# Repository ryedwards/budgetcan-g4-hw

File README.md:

# BudgetCAN G4

Hardware files for a simple CAN and LIN device built around an STM32 G4 MCU

## Description

The BudgetCAN G4 Hardware is designed to implement the full CAN potential of the STM32G4 MCU.  The hardware has been designed with the following features:
* USB-C connector for robust connectivity to a host machine
* 3 CANFD channels each with SW selectable termination resistors
* 1 LIN channel with SW selectable master pull-up
* 12V power input provides power for LIN and a 3A 5V regulator
* Debug header pinout for STLINK v3 Mini 14-pin connector - the VCP pins are routed to a UART for debugging
* Onboard 8Mhz crystal provides high clock accuracy for CANFD
* 5V power MUX to ensure graceful handoff between USB and 12V power supplies
* 3x configurable LEDs for status indications
* Automotive grade Molex Mini50 connector
* 4 layer PCB
* BOM cost under $15USD

## File usage

* The HW was designed with KiCad8
* Part BOM included with the schematic is complete for JLCPCB parts

## Firmware
Firmware is available for this hardware in the budgetcan firmware repository.  This firmware is based on the gs_usb driver and currently is fully supported in Linux and will work in Windows using the same drivers that have been developed for gs_usb.
* https://github.com/ryedwards/budgetcan-fw

You can also use the included STM32CubeMX .ioc file to generate your own firmware.  

This hardware can also be used as a standalone device (gateway module, simulated ECU, etc) since it has a 12V input and can be used headless.

## Help

If you find any issues with the hardware please submit an issue into GitHub

## License

This project is licensed under the MIT License - see the LICENSE.md file for details

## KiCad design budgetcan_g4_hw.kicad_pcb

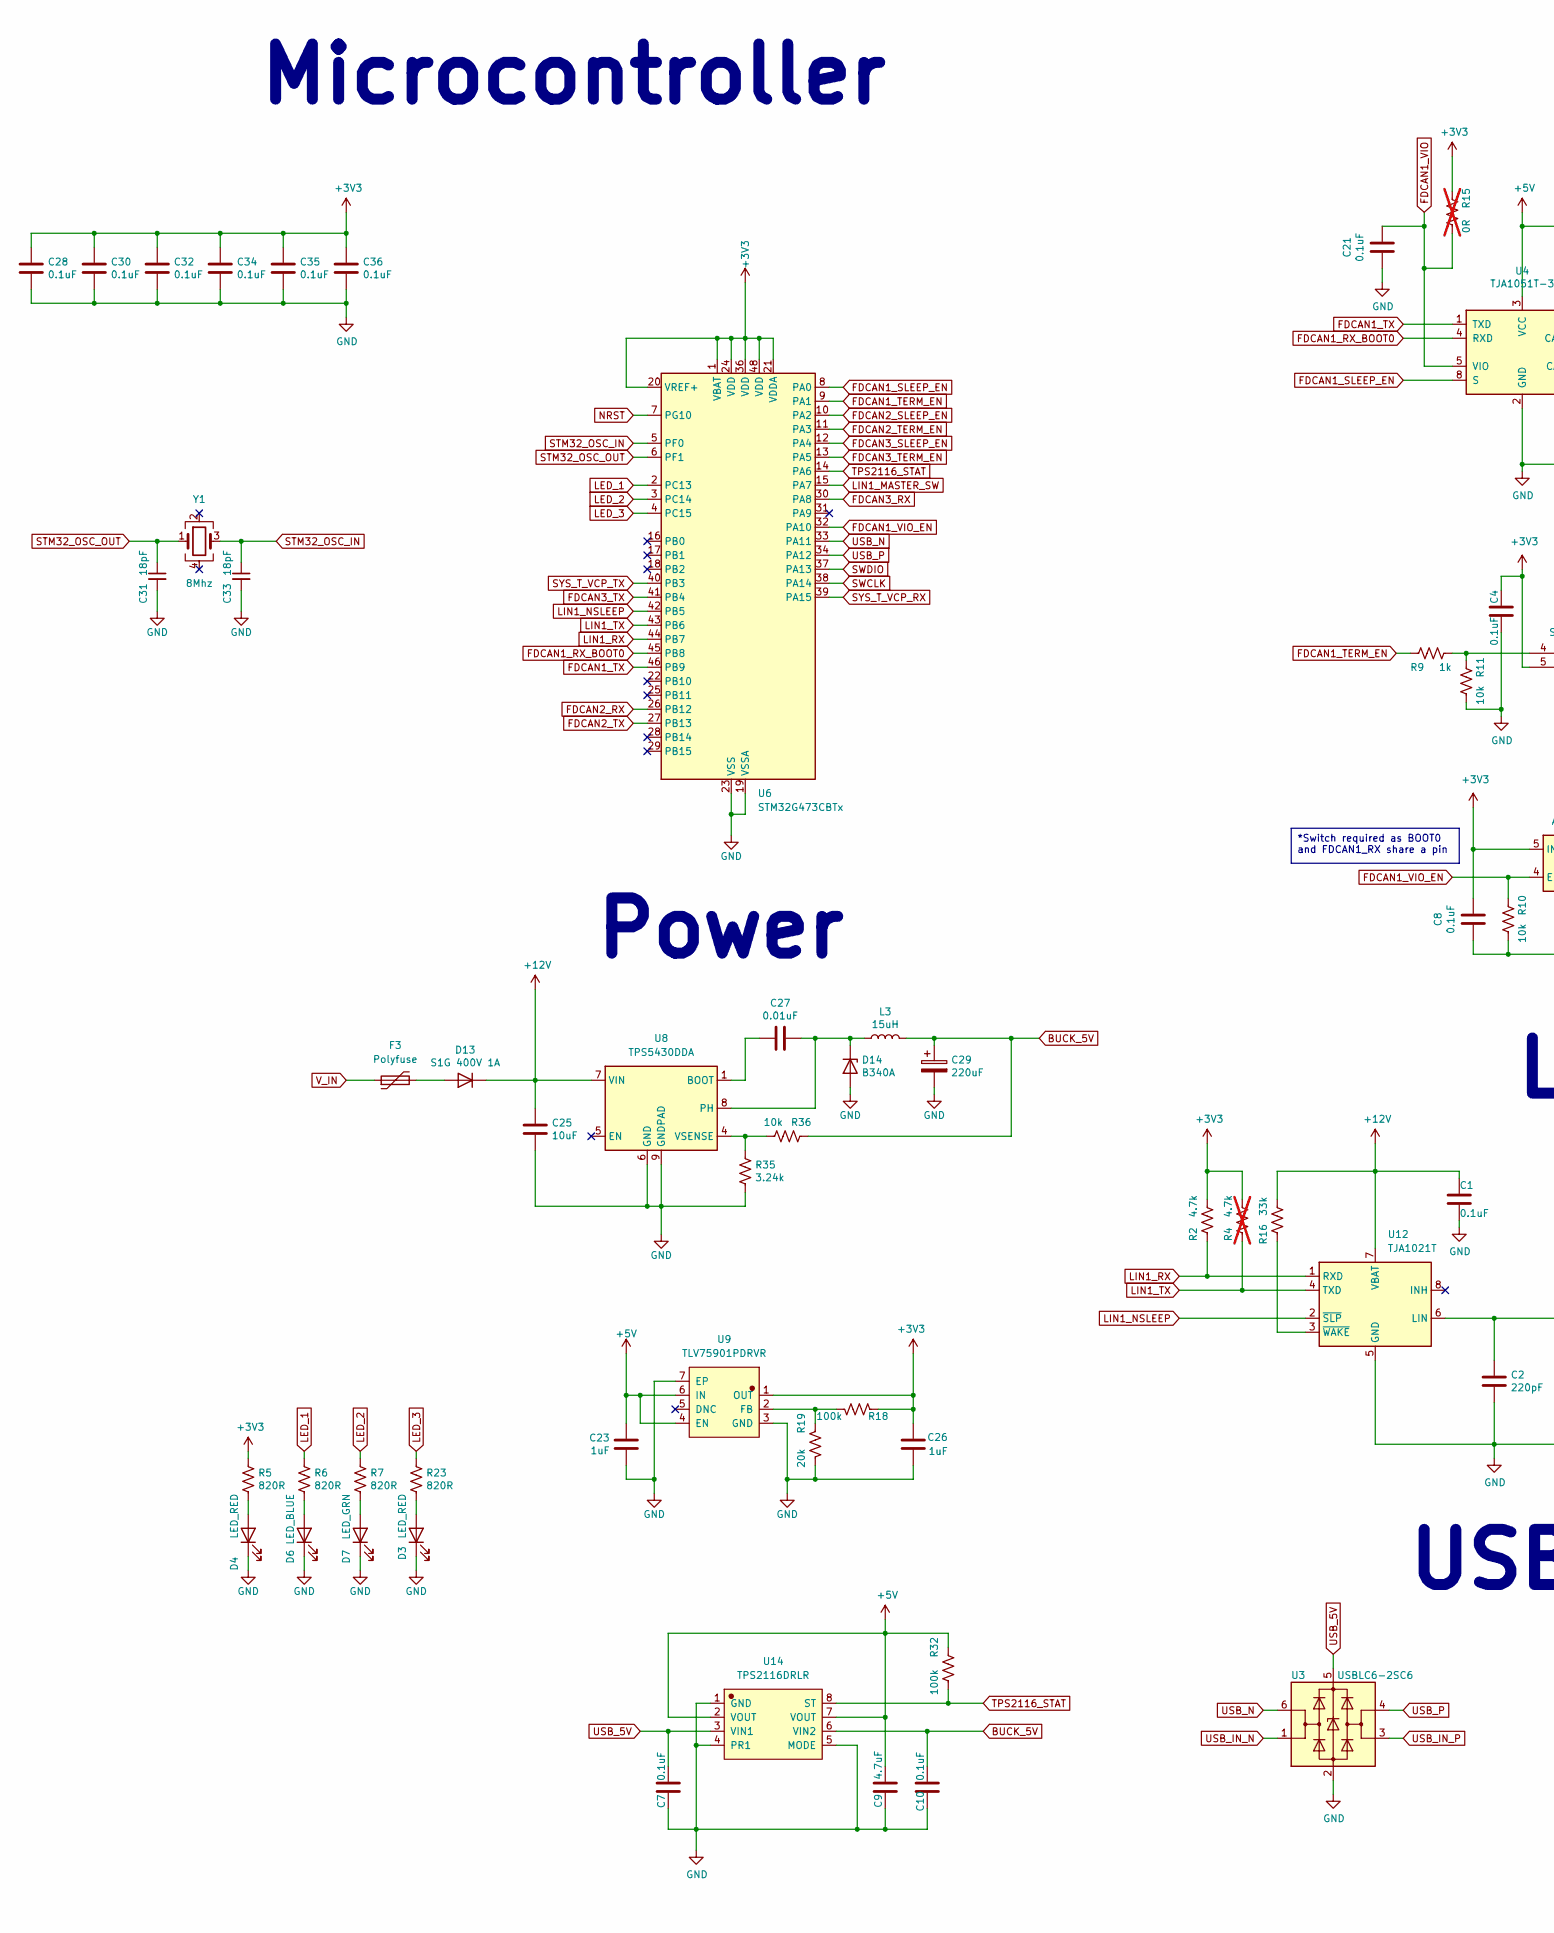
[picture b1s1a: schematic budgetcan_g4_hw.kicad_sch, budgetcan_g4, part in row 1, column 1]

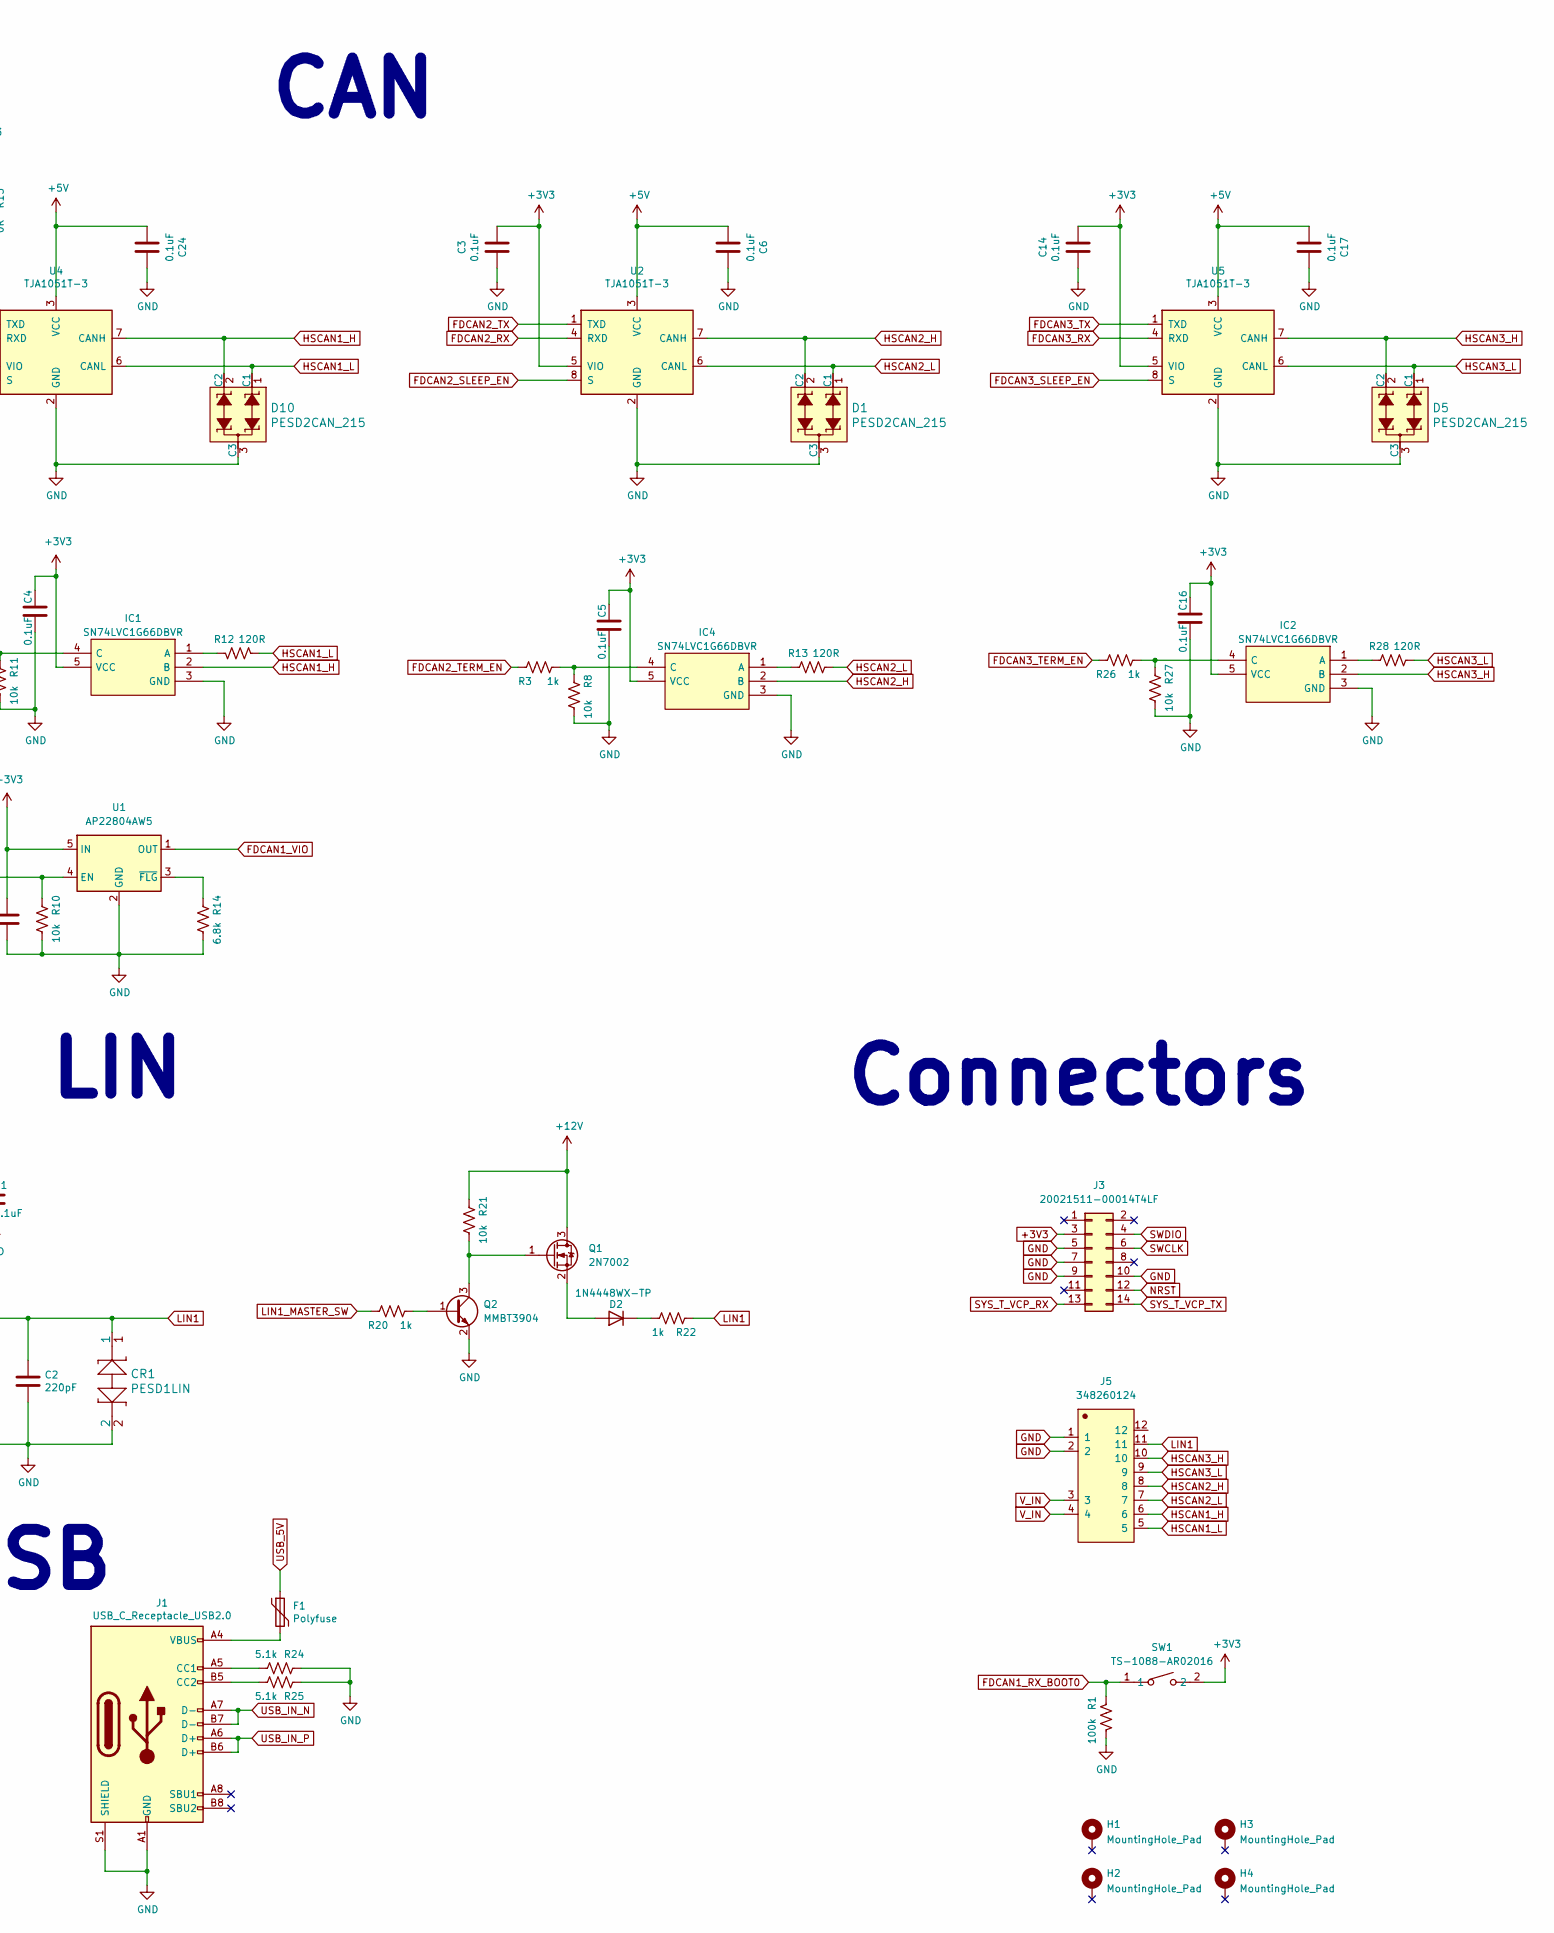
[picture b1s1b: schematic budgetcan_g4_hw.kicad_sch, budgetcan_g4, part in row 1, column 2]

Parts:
C1, C3, C4, C5, C6, C8, C14, C16, C17, C21, C24: 0.1uF; C_0402_1005Metric; Manufacturer_Part_Number CC0603KRX7R8BB104; LCSC Part # C1525
C2: 220pF; C_0402_1005Metric; Manufacturer_Part_Number CC0603JRNPO9BN221; LCSC Part # C1530
C7, C10: 0.1uF; C_0603_1608Metric; Manufacturer_Part_Number CC0603KRX7R8BB104; LCSC Part # C14663
C9: 4.7uF; C_0603_1608Metric; LCSC Part # C19666
C23, C26: 1uF; C_0603_1608Metric; LCSC Part # C15849
C25: 10uF; C_1206_3216Metric; Manufacturer_Part_Number CL31B106KQHNFNE; LCSC Part # C13585
C27: 0.01uF; C_0603_1608Metric; LCSC Part # C57112
C28, C30, C32, C34, C35, C36: 0.1uF; C_0402_1005Metric; LCSC Part # C1525
C29: 220uF; CP_Elec_6.3x5.4; LCSC Part # C88676
C31, C33: 18pF; C_0402_1005Metric; LCSC Part # C1549
CR1: PESD1LIN; D_SOD-323; Manufacturer_Part_Number PESD1LIN,135; LCSC Part # C2831530
D1, D5, D10: PESD2CAN_215; SOT-23; MPN PESD2CAN,215; Digi-Key_PN 1727-3891-1-ND
D2: ‎1N4448WX-TP‎; D_SOD-323; Manufacturer_Part_Number ‎1N4448WX-TP‎; Digi-Key_PN 1N4448WXTPMSCT-ND
D3, D4: LED_RED; LED_0805_2012Metric; LCSC Part # C84256
D6: LED_BLUE; LED_0805_2012Metric; LCSC Part # C965817
D7: LED_GRN; LED_0805_2012Metric; LCSC Part # C2297
D13: S1G 400V 1A; D_SMA; Manufacturer_Part_Number S1G; LCSC Part # C95872
D14: B340A; D_SMA; LCSC Part # C3018525
F1: Polyfuse; Fuse_0805_2012Metric; Manufacturer_Part_Number 0ZCK0035FF2G; LCSC Part # C2833485
F3: Polyfuse; F1812; Manufacturer_Part_Number 0ZCG0200AF2B; Digi-Key_PN 507-2074-1-ND
H1, H2, H3, H4: MountingHole_Pad; MountingHole_3.2mm_M3_Pad_TopBottom
IC1, IC2, IC4: SN74LVC1G66DBVR; SOT-23-5; Manufacturer_Part_Number SN74LVC1G66DBVR; LCSC Part # C5375974
J1: USB_C_Receptacle_USB2.0; USB_C_Receptacle_Palconn_UTC16-G; Manufacturer_Part_Number USB4085-GF-A; Digi-Key_PN 2073-USB4085-GF-ACT-ND
J3: 20021511-00014T4LF; PinHeader_2x07_P1.27mm_Vertical; Mouser Part Number 200-FTSH10701LDK
J5: 348260124; CONN-TH_348260124; LCSC Part # C587298
L3: 15uH; L_Bourns_SRP7028A_7.3x6.6mm; LCSC Part # C5189959
Q1: 2N7002; SOT-23; LCSC Part # C8545
Q2: MMBT3904; SOT-23; LCSC Part # C20526
R1: 100k; R_0603_1608Metric; Manufacturer_Part_Number RC0603FR-07100KL; LCSC Part # C25803
R2: 4.7k; R_0402_1005Metric; Manufacturer_Part_Number RC0603JR-074K7L; LCSC Part # C25900
R3, R9, R20, R22, R26: 1k; R_0402_1005Metric; Manufacturer_Part_Number RC0603FR-071KL; LCSC Part # C11702
R4: 4.7k; R_0402_1005Metric; LCSC Part # C25900; not fitted
R5, R6, R7, R23: 820R; R_0603_1608Metric; Manufacturer_Part_Number RC0603FR-071KL; LCSC Part # C23253
R8, R10, R11, R21, R27: 10k; R_0402_1005Metric; Manufacturer_Part_Number RC0603FR-0710KL; LCSC Part # C25744
R12, R13, R28: 120R; R_0402_1005Metric; Manufacturer_Part_Number RC0603FR-07120RL; LCSC Part # C25079
R14: 6.8k; R_0402_1005Metric; Manufacturer_Part_Number RC0603FR-0710KL; LCSC Part # C25917
R15: 0R; R_0402_1005Metric; LCSC Part # C17168; not fitted
R16: 33k; R_0402_1005Metric; Manufacturer_Part_Number RC0603FR-0733K2L; LCSC Part # C25779
R18: 100k; R_0603_1608Metric; Manufacturer_Part_Number RC0603FR-0710KL; LCSC Part # C25803
R19: 20k; R_0603_1608Metric; Manufacturer_Part_Number RC0603FR-0710KL; LCSC Part # C4184
R24, R25: 5.1k; R_0603_1608Metric; Manufacturer_Part_Number RC0603JR-075K1L; LCSC Part # C23186
R32: 100k; R_0402_1005Metric; Manufacturer_Part_Number RC0603FR-0710KL; LCSC Part # C25741
R35: 3.24k; R_0603_1608Metric; LCSC Part # C22994
R36: 10k; R_0603_1608Metric; LCSC Part # C25804
SW1: TS-1088-AR02016; SW-SMD_L3.9-W3.0-P4.45; LCSC Part # C720477
U1: AP22804AW5; SOT-23-5; LCSC Part # C89855
U2, U4, U5: TJA1051T-3; SOIC-8_3.9x4.9mm_P1.27mm; LCSC Part # C38695
U3: USBLC6-2SC6; SOT-23-6; Manufacturer_Part_Number USBLC6-2SC6; LCSC Part # C2687116
U6: STM32G473CBTx; LQFP-48_7x7mm_P0.5mm; LCSC Part # C730111
U8: TPS5430DDA; TI_SO-PowerPAD-8_ThermalVias; LCSC Part # C9864
U9: TLV75901PDRVR; WSON-6_L2.0-W2.0-P0.65-TL-EP; LCSC Part # C544759
U12: TJA1021T; SOIC-8_3.9x4.9mm_P1.27mm; LCSC Part # C128810
U14: TPS2116DRLR; SOT-583-8_L2.1-W1.6-P0.50-LS1.6-BL; LCSC Part # C3235557
Y1: 8Mhz; Crystal_SMD_3225-4Pin_3.2x2.5mm; LCSC Part # C963531

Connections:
+3V3: C3.1, C4.1, C5.1, C8.1, C14.1, C16.1, C26.1, C28.1, C30.1, C32.1, C34.1, C35.1, C36.1, IC1.5 (VCC), IC2.5 (VCC), IC4.5 (VCC), J3.3, R2.2, R4.2, R5.2, R15.1, R18.1, SW1.2, U1.5 (IN), U2.5 (VIO), U5.5 (VIO), U6.1 (VBAT), U6.20 (VREF+), U6.21 (VDDA), U6.24 (VDD), U6.36 (VDD), U6.48 (VDD), U9.1 (OUT)
+5V: C6.2, C9.1, C17.2, C23.1, C24.2, R32.1, U2.3 (VCC), U4.3 (VCC), U5.3 (VCC), U9.4 (EN), U9.6 (IN), U14.2 (VOUT), U14.7 (VOUT)
+12V: C1.1, C25.1, D13.1 (K), Q1.3 (D), R16.2, R21.1, U8.7 (VIN), U12.7 (VBAT)
BUCK_5V: C10.1, C29.1, L3.2, R36.2, U14.6 (VIN2)
FDCAN1_RX_BOOT0: R1.1, SW1.1, U4.4 (RXD), U6.45 (PB8)
FDCAN1_SLEEP_EN: U4.8 (S), U6.8 (PA0)
FDCAN1_TERM_EN: R9.1, U6.9 (PA1)
FDCAN1_TX: U4.1 (TXD), U6.46 (PB9)
FDCAN1_VIO: C21.1, R15.2, U1.1 (OUT), U4.5 (VIO)
FDCAN1_VIO_EN: R10.1, U1.4 (EN), U6.32 (PA10)
FDCAN2_RX: U2.4 (RXD), U6.26 (PB12)
FDCAN2_SLEEP_EN: U2.8 (S), U6.10 (PA2)
FDCAN2_TERM_EN: R3.1, U6.11 (PA3)
FDCAN2_TX: U2.1 (TXD), U6.27 (PB13)
FDCAN3_RX: U5.4 (RXD), U6.30 (PA8)
FDCAN3_SLEEP_EN: U5.8 (S), U6.12 (PA4)
FDCAN3_TERM_EN: R26.1, U6.13 (PA5)
FDCAN3_TX: U5.1 (TXD), U6.41 (PB4)
GND: C1.2, C2.2, C3.2, C4.2, C5.2, C6.1, C7.2, C8.2, C9.2, C10.2, C14.2, C16.2, C17.1, C21.2, C23.2, C24.1, C25.2, C26.2, C28.2, C29.2, C30.2, C31.2, C32.2, C33.2, C34.2, C35.2, C36.2, CR1.2, D1.3 (C3), D3.1 (K), D4.1 (K), D5.3 (C3), D6.1 (K), D7.1 (K), D10.3 (C3), D14.2 (A), IC1.3 (GND), IC2.3 (GND), IC4.3 (GND), J1.A1 (GND), J1.A12 (GND), J1.B1 (GND), J1.B12 (GND), J1.S1 (SHIELD), J3.5, J3.7, J3.9, J3.10, J5.1, J5.2, Q2.2 (E), R1.2, R8.2, R10.2, R11.2, R14.2, R19.2, R24.1, R25.1, R27.2, R35.2, U1.2 (GND), U2.2 (GND), U3.2 (GND), U4.2 (GND), U5.2 (GND), U6.19 (VSSA), U6.23 (VSS), U6.35 (VSS), U6.47 (VSS), U8.6 (GND), U8.9 (GNDPAD), U9.3 (GND), U9.7 (EP), U12.5 (GND), U14.1 (GND), U14.4 (PR1), U14.5 (MODE)
HSCAN1_H: D10.2 (C2), IC1.2 (B), J5.6, U4.7 (CANH)
HSCAN1_L: D10.1 (C1), J5.5, R12.2, U4.6 (CANL)
HSCAN2_H: D1.2 (C2), IC4.2 (B), J5.8, U2.7 (CANH)
HSCAN2_L: D1.1 (C1), J5.7, R13.2, U2.6 (CANL)
HSCAN3_H: D5.2 (C2), IC2.2 (B), J5.10, U5.7 (CANH)
HSCAN3_L: D5.1 (C1), J5.9, R28.2, U5.6 (CANL)
LED_1: R6.2, U6.2 (PC13)
LED_2: R7.2, U6.3 (PC14)
LED_3: R23.2, U6.4 (PC15)
LIN1: C2.1, CR1.1, J5.11, R22.1, U12.6 (LIN)
LIN1_MASTER_SW: R20.1, U6.15 (PA7)
LIN1_NSLEEP: U6.42 (PB5), U12.2 (~SLP)
LIN1_RX: R2.1, U6.44 (PB7), U12.1 (RXD)
LIN1_TX: R4.1, U6.43 (PB6), U12.4 (TXD)
NRST: J3.12, U6.7 (PG10)
unnamed: D2.2 (A), Q1.2 (S)
unnamed: D2.1 (K), R22.2
unnamed: D3.2 (A), R23.1
unnamed: D4.2 (A), R5.1
unnamed: D6.2 (A), R6.1
unnamed: D7.2 (A), R7.1
unnamed: D13.2 (A), F3.2
unnamed: C27.1, D14.1 (K), L3.1, U8.8 (PH)
unnamed: F1.2, J1.A4 (VBUS), J1.A9 (VBUS), J1.B4 (VBUS), J1.B9 (VBUS)
unnamed: IC1.1 (A), R12.1
unnamed: IC1.4 (C), R9.2, R11.1
unnamed: IC2.1 (A), R28.1
unnamed: IC2.4 (C), R26.2, R27.1
unnamed: IC4.1 (A), R13.1
unnamed: IC4.4 (C), R3.2, R8.1
unnamed: J1.A5 (CC1), R24.2
unnamed: J1.B5 (CC2), R25.2
unnamed: Q1.1 (G), Q2.3 (C), R21.2
unnamed: Q2.1 (B), R20.2
unnamed: R14.1, U1.3 (~FLG)
unnamed: C27.2, U8.1 (BOOT)
unnamed: R35.1, R36.1, U8.4 (VSENSE)
unnamed: R18.2, R19.1, U9.2 (FB)
unnamed: R16.1, U12.3 (~WAKE)
STM32_OSC_IN: C33.1, U6.5 (PF0), Y1.3
STM32_OSC_OUT: C31.1, U6.6 (PF1), Y1.1
SWCLK: J3.6, U6.38 (PA14)
SWDIO: J3.4, U6.37 (PA13)
SYS_T_VCP_RX: J3.13, U6.39 (PA15)
SYS_T_VCP_TX: J3.14, U6.40 (PB3)
TPS2116_STAT: R32.2, U6.14 (PA6), U14.8 (ST)
USB_5V: C7.1, F1.1, U3.5 (VBUS), U14.3 (VIN1)
USB_IN_N: J1.A7 (D-), J1.B7 (D-), U3.1 (I/O1)
USB_IN_P: J1.A6 (D+), J1.B6 (D+), U3.3 (I/O2)
USB_N: U3.6 (I/O1), U6.33 (PA11)
USB_P: U3.4 (I/O2), U6.34 (PA12)
V_IN: F3.1, J5.3, J5.4

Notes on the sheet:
*Switch required as BOOT0 and FDCAN1_RX share a pin
LIN
Microcontroller
CAN
Power
USB
Connectors

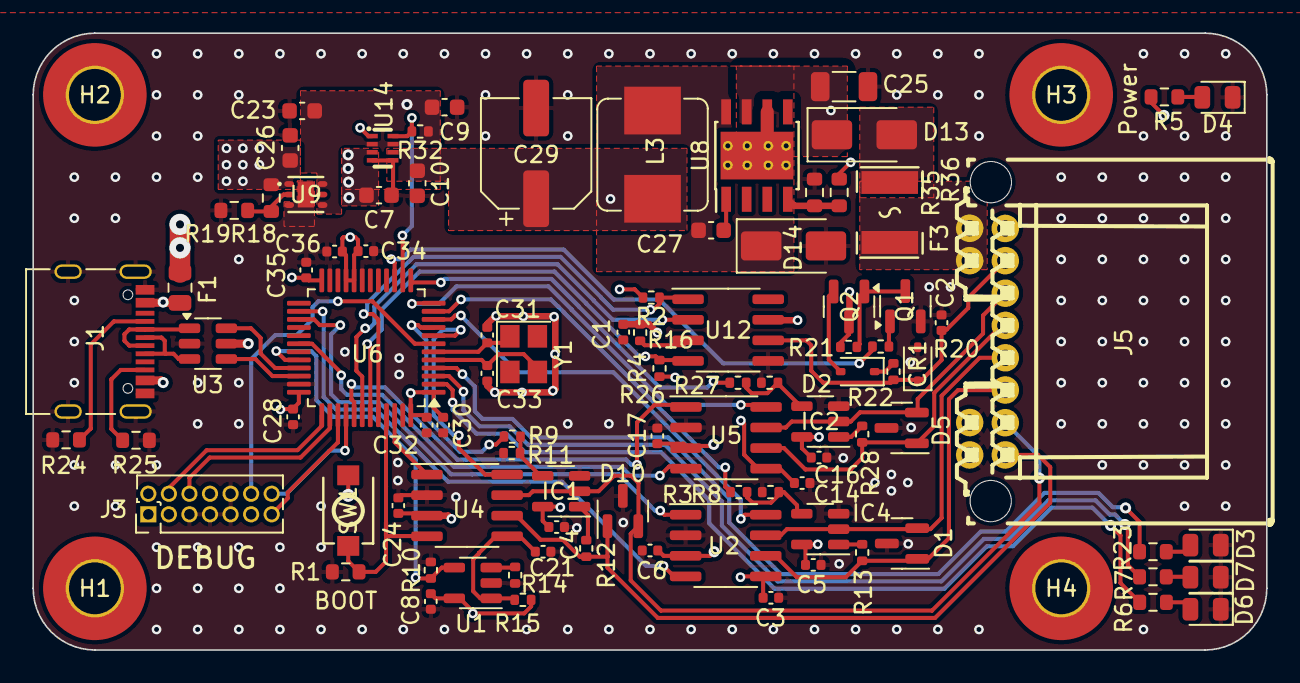
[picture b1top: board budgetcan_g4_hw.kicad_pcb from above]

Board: 4 copper layers, 76.2 x 38.1 mm, 96 parts (0 on the bottom side), 71 nets.

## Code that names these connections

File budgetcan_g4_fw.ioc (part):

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Mcu.Name=STM32G473C(B-C-E)Tx
Mcu.Package=LQFP48
Mcu.UserName=STM32G473CBTx
PA0.GPIOParameters=GPIO_Label
PA0.GPIO_Label=FDCAN1_SLEEP_EN
PA0.Signal=GPIO_Output
PA1.GPIOParameters=GPIO_Label
PA1.GPIO_Label=FDCAN1_TERM_EN
PA1.Signal=GPIO_Output
PA10.GPIOParameters=GPIO_Label
PA10.GPIO_Label=FDCAN1_VIO_EN
PA10.Signal=GPIO_Output
PA11.Mode=Device
PA11.Signal=USB_DM
PA12.Mode=Device
PA12.Signal=USB_DP
PA13.Mode=Serial_Wire
PA13.Signal=SYS_JTMS-SWDIO
PA14.Mode=Serial_Wire
PA14.Signal=SYS_JTCK-SWCLK
PA15.Mode=Asynchronous
PA15.Signal=USART2_RX
PA2.GPIOParameters=GPIO_Label
PA2.GPIO_Label=FDCAN2_SLEEP_EN
PA2.Signal=GPIO_Output
PA3.GPIOParameters=GPIO_Label
PA3.GPIO_Label=FDCAN2_TERM_EN
PA3.Signal=GPIO_Output
PA4.GPIOParameters=GPIO_Label
PA4.GPIO_Label=FDCAN3_SLEEP_EN
PA4.Signal=GPIO_Output
PA5.GPIOParameters=GPIO_Label
PA5.GPIO_Label=FDCAN3_TERM_EN
PA5.Signal=GPIO_Output
PA6.GPIOParameters=GPIO_Label
PA6.GPIO_Label=TPS2116_STAT
PA6.Signal=GPIO_Input
PA7.GPIOParameters=GPIO_Label
PA7.GPIO_Label=LIN1_MASTER_EN
PA7.Signal=GPIO_Output
PA8.Mode=FDCAN_Activate
PA8.Signal=FDCAN3_RX
PB12.Mode=FDCAN_Activate
PB12.Signal=FDCAN2_RX
PB13.Mode=FDCAN_Activate
PB13.Signal=FDCAN2_TX
PB3.Mode=Asynchronous
PB3.Signal=USART2_TX
PB4.Mode=FDCAN_Activate
PB4.Signal=FDCAN3_TX
PB5.GPIOParameters=GPIO_Label
PB5.GPIO_Label=LIN1_nSLEEP
PB5.Signal=GPIO_Output
PB6.Mode=LIN
PB6.Signal=USART1_TX
PB7.Mode=LIN
PB7.Signal=USART1_RX
PB8-BOOT0.Mode=FDCAN_Activate
PB8-BOOT0.Signal=FDCAN1_RX
PB9.Mode=FDCAN_Activate
PB9.Signal=FDCAN1_TX
PC13.GPIOParameters=GPIO_Label
PC13.GPIO_Label=LED1
PC13.Signal=GPIO_Output
PC14-OSC32_IN.GPIOParameters=GPIO_Label
PC14-OSC32_IN.GPIO_Label=LED2
PC14-OSC32_IN.Signal=GPIO_Output
PC15-OSC32_OUT.GPIOParameters=GPIO_Label
PC15-OSC32_OUT.GPIO_Label=LED3
PC15-OSC32_OUT.Signal=GPIO_Output
PF0-OSC_IN.Mode=HSE-External-Oscillator
PF0-OSC_IN.Signal=RCC_OSC_IN
PF1-OSC_OUT.Mode=HSE-External-Oscillator
PF1-OSC_OUT.Signal=RCC_OSC_OUT
RCC.SYSCLKFreq_VALUE=160000000
RCC.SYSCLKSource=RCC_SYSCLKSOURCE_PLLCLK
board=custom

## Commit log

2024-02-19 Fix the LCSC part number for the CAN termination switch
2024-03-04 Fix incorrect connection of the 3.3V regulator feedback resistors
2024-03-07 Update to KiCad 8 and fix USB pinouts
2024-07-09 Changes to fix issues found with prototype
    - Fixed the power feed for FDCAN1 from switching the 5V feed (VCC) to the 3.3V feed (VIO)
    - Changed the XTAL to 8Mhz
    - Added a SW controlled master switch for LIN
    - Changed the boot selector to a button switch
2024-07-09 Update README and upload the .ioc file
